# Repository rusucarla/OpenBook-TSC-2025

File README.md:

# Proiect TSC 2025 - OpenBook

## 1.O diagramă bloc cu toate componentele proiectului și cum sunt ele legate

```mermaid
graph TD
    
    USB["USB-C Connector(ESD Protection)"] -->|5V| CHG["Battery Charger (MCP73831)"]
    CHG -->|Charging| BATT["Li-Po Battery (2500mAh)"]
    BATT --> LDO["3.3V LDO Regulator (XC6220)"]

    LDO -->|3.3V| ESP["ESP32-C6-WROOM-1(MCU)"]

    ESP -- I2C --> RTC["Real Time Clock(DS3231)"]
    ESP -- I2C --> BME["Environmental Sensor(BME688)"]
    ESP -- I2C --> FUEL["Battery Fuel Gauge(MAX17048)"]
    ESP -- I2C --> QWIIC["Qwiic / Stemma QT"]

    ESP -- SPI --> FLASH["External NOR Flash(W25Q512)"]
    ESP -- SPI --> SD["MicroSD Card Slot"]
    ESP -- SPI --> EPD_HEADER["E-Paper Display Header"]

    EPD_HEADER --> EPD_DRIVER["EPD Driver Circuit"]
    EPD_DRIVER --> EPD_POW["EPD HV Power"]
    LDO --> EPD_HEADER

    ESP -- GPIO --> BUTTONS["3x Buttons:BOOT, CHANGE, RESET"]

    USB -- USB D+/D- --> ESP
```
## 2. BOM-ul (coloanele cu N/A sunt duplicate ale unui tip de componentă și am pus date doar la prima apariție a acelui tip de componentă)

Încă o observație, TP-ul si SJ-urile au fost modelate de către mine și astfel nu au model cu link sau data sheet.

| Name of component | Device                                       | Check Prices                                                                                                | DataSheet                                                                                                 |
|-------------------|----------------------------------------------|-----------------------------------------------------------------------------------------------------------------|---------------------------------------------------------------------------------------------------------------|
| BOOT_BUTTON       | BUTTON_CUSYOMV1                             | https://industry.panasonic.com/global/en/products/control/switch/light-touch/number/evqpuj02k                  | https://industry.panasonic.com/global/en/products/control/switch/light-touch/number/evqpuj02k                  |
| C1                | ESP32_WROVER_EAGLE-LTSPICE_CC0402            | https://industry.panasonic.com/global/en/products/control/switch/light-touch/number/evqpuj02k                  | https://industry.panasonic.com/global/en/products/control/switch/light-touch/number/evqpuj02k                  |
| C1_BAT            | ESP32_WROVER_EAGLE-LTSPICE_CC0402            | #N/A                                                                                                            | #N/A                                                                                                           |
| C1_BAT1           | EAGLE-LTSPICE_CC0402                         | #N/A                                                                                                            | #N/A                                                                                                           |
| C1_BAT2           | EAGLE-LTSPICE_CC0402                         | #N/A                                                                                                            | #N/A                                                                                                           |
| C2                | ESP32_WROVER_EAGLE-LTSPICE_CC0402            | #N/A                                                                                                            | #N/A                                                                                                           |
| C2_BAT\           | ESP32_WROVER_EAGLE-LTSPICE_CC0402            | #N/A                                                                                                            | #N/A                                                                                                           |
| C3                | RCL_CPOL-EUCT3528                            | #N/A                                                                                                            | #N/A                                                                                                           |
| C4                | ESP32_WROVER_EAGLE-LTSPICE_CC0402            | #N/A                                                                                                            | #N/A                                                                                                           |
| C4_USB            | ESP32_WROVER_EAGLE-LTSPICE_CC0402            | #N/A                                                                                                            | #N/A                                                                                                           |
| C5                | ESP32_WROVER_EAGLE-LTSPICE_CC0402            | #N/A                                                                                                            | #N/A                                                                                                           |
| C5_USB            | ESP32_WROVER_EAGLE-LTSPICE_CC0402            | #N/A                                                                                                            | #N/A                                                                                                           |
| C6                | ESP32_WROVER_EAGLE-LTSPICE_CC0402            | #N/A                                                                                                            | #N/A                                                                                                           |
| C7                | ESP32_WROVER_EAGLE-LTSPICE_CC0402            | #N/A                                                                                                            | #N/A                                                                                                           |
| C8                | ESP32_WROVER_EAGLE-LTSPICE_CC0402            | #N/A                                                                                                            | #N/A                                                                                                           |
| C9                | EAGLE-LTSPICE_CC0402                         | #N/A                                                                                                            | #N/A                                                                                                           |
| C10               | ESP32_WROVER_EAGLE-LTSPICE_CC0402            | #N/A                                                                                                            | #N/A                                                                                                           |
| C10_SUPERCAP      | CPH3225A                                     | https://www.snapeda.com/parts/CPH3225A/Seiko+Instruments/view-part/?ref=eda                                   | https://www.snapeda.com/parts/CPH3225A/Seiko+Instruments/view-part/?ref=eda                                   |
| CHANGE_BUTTON     | BUTTON_CUSYOMV1                             | https://industry.panasonic.com/global/en/products/control/switch-light-touch/number/evqpuj02k                  | https://industry.panasonic.com/global/en/products/control/switch-light-touch/number/evqpuj02k                  |
| CHG_LED           | ADAFRUIT_LEDCHIP-LED0603                     | https://www.snapeda.com/parts/KP-1608SURCK/Kingbright/view-part/?ref=search&t=LED%200603                       | https://www.snapeda.com/parts/KP-1608SURCK/Kingbright/view-part/?ref=search&t=LED%200603                       |
| C_DELAY           | ESP32_WROVER_EAGLE-LTSPICE_CC0402            | #N/A                                                                                                            | #N/A                                                                                                           |
| D1                | USBLC6-2SC6Y                                 | https://www.snapeda.com/parts/USBLC6-2SC6Y/STMicroelectronics/view-part/?ref=eda                              | https://www.snapeda.com/parts/USBLC6-2SC6Y/STMicroelectronics/view-part/?ref=eda                              |
| D2                | ESP32_WROVER_AVX---SD0805S020S1R0_AVX_...    | https://eu.mouser.com/ProductDetail/KYOCERA-AVX/SD0805S020S1R0?qs=jCA%252BPfw4LHbpkAoSnwrdjw%3D%3D              | http://datasheets.avx.com/schottky.pdf                                                                         |
| D3                | MBR0530                                      | https://eu.mouser.com/ProductDetail/KYOCERA-AVX/SD0805S020S1R0?qs=jCA%252BPfw4LHbpkAoSnwrdjw%3D%3D              | https://eu.mouser.com/ProductDetail/KYOCERA-AVX/SD0805S020S1R0?qs=jCA%252BPfw4LHbpkAoSnwrdjw%3D%3D              |
| D4                | MBR0530                                      | https://www.snapeda.com/parts/MBR0530/Onsemi/view-part/?ref=eda                                                | https://www.snapeda.com/parts/MBR0530/Onsemi/view-part/?ref=eda                                                |
| D5                | MBR0530                                      | https://www.snapeda.com/parts/MBR0530/Onsemi/view-part/?ref=eda                                                | https://www.snapeda.com/parts/MBR0530/Onsemi/view-part/?ref=eda                                                |
| D6                | PGB1010603MR                                 | https://www.snapeda.com/parts/PGB1010603MR/Littelfuse/view-part/?ref=eda                                      | https://www.snapeda.com/parts/PGB1010603MR/Littelfuse/view-part/?ref=eda                                      |
| D7                | ESP32_WROVER_AVX---SD0805S020S1R0_AVX_...    | https://eu.mouser.com/ProductDetail/KYOCERA-AVX/SD0805S020S1R0?qs=jCA%252BPfw4LHbpkAoSnwrdjw%3D%3D              | http://datasheets.avx.com/schottky.pdf                                                                         |
| D8                | PGB1010603MR                                 | https://www.snapeda.com/parts/PGB1010603MR/Littelfuse/view-part/?ref=eda                                      | https://www.snapeda.com/parts/PGB1010603MR/Littelfuse/view-part/?ref=eda                                      |
| D9                | PGB1010603MR                                 | https://www.snapeda.com/parts/PGB1010603MR/Littelfuse/view-part/?ref=eda                                      | https://www.snapeda.com/parts/PGB1010603MR/Littelfuse/view-part/?ref=eda                                      |
| D10               | PGB1010603MR                                 | https://www.snapeda.com/parts/PGB1010603MR/Littelfuse/view-part/?ref=eda                                      | https://www.snapeda.com/parts/PGB1010603MR/Littelfuse/view-part/?ref=eda                                      |
| D11               | PGB1010603MR                                 | https://www.snapeda.com/parts/PGB1010603MR/Littelfuse/view-part/?ref=eda                                      | https://www.snapeda.com/parts/PGB1010603MR/Littelfuse/view-part/?ref=eda                                      |
| D12               | PGB1010603MR                                 | https://www.snapeda.com/parts/PGB1010603MR/Littelfuse/view-part/?ref=eda                                      | https://www.snapeda.com/parts/PGB1010603MR/Littelfuse/view-part/?ref=eda                                      |
| EPD_C1            | ESP32_WROVER_EAGLE-LTSPICE_CC0402            | #N/A                                                                                                            | #N/A                                                                                                           |
| EPD_C2            | ESP32_WROVER_EAGLE-LTSPICE_CC0402            | #N/A                                                                                                            | #N/A                                                                                                           |
| EPD_C5            | ESP32_WROVER_EAGLE-LTSPICE_CC0402            | #N/A                                                                                                            | #N/A                                                                                                           |
| EPD_C6            | ESP32_WROVER_EAGLE-LTSPICE_CC0402            | #N/A                                                                                                            | #N/A                                                                                                           |
| EPD_C7            | ESP32_WROVER_EAGLE-LTSPICE_CC0402            | #N/A                                                                                                            | #N/A                                                                                                           |
| EPD_C8            | ESP32_WROVER_EAGLE-LTSPICE_CC0402            | #N/A                                                                                                            | #N/A                                                                                                           |
| EPD_C9            | ESP32_WROVER_EAGLE-LTSPICE_CC0402            | #N/A                                                                                                            | #N/A                                                                                                           |
| EPD_C10           | ESP32_WROVER_EAGLE-LTSPICE_CC0402            | #N/A                                                                                                            | #N/A                                                                                                           |
| EPD_C11           | ESP32_WROVER_EAGLE-LTSPICE_CC0402            | #N/A                                                                                                            | #N/A                                                                                                           |
| EPD_C12           | ESP32_WROVER_EAGLE-LTSPICE_CC0402            | #N/A                                                                                                            | #N/A                                                                                                           |
| IC1               | BD5229G-TR                                   | https://componentsearchengine.com/part-view/BD5229G-TR/ROHM%20Semiconductor                                    | https://componentsearchengine.com/part-view/BD5229G-TR/ROHM%20Semiconductor                                    |
| IC4               | XC6220A331MR-G                               | https://componentsearchengine.com/part-view/XC6220A331MR-G/Torex                                              | https://componentsearchengine.com/part-view/XC6220A331MR-G/Torex                                              |
| J1                | FH34SRJ-24S-0.5SH_99_                        | https://componentsearchengine.com/part-view/XC6220A331MR-G/Torex                                              | https://componentsearchengine.com/part-view/XC6220A331MR-G/Torex                                              |
| J2                | SAMACSYS_PARTS_USB4110-GF-A                  | https://componentsearchengine.com/part-view/USB4110-GF-A/GCT%20(GLOBAL%20CONNECTOR%20TECHNOLOGY               | https://componentsearchengine.com/part-view/USB4110-GF-A/GCT%20(GLOBAL%20CONNECTOR%20TECHNOLOGY               |
| J3                | QWIIC_CONNECTORJS-1MM                        | #N/A                                                                                                            | #N/A                                                                                                           |
| J4                | 112A-TAAR-R03_ATTEND                         | https://store.comet.srl.ro/Catalogue/Product/43497/                                                            | https://store.comet.srl.ro/Catalogue/Product/43497/                                                            |
| L1                | 744043680IND_4828-WE-TPC_WRE                 | https://eu.mouser.com/ProductDetail/Wurth-Elektronik/744043680?qs=PGXP4M47uW6VkZq%252BkzjrHA%3D%3D               | https://eu.mouser.com/ProductDetail/Wurth-Elektronik/744043680?qs=PGXP4M47uW6VkZq%252BkzjrHA%3D%3D               |
| PFMF.050.1        | ESP32C6_VARISTORCN1812                       | https://www.mouser.co.uk/ProductDetail/EPCOS-TDK/B72520T0350K062?qs=dEfas%2FXlABIszF52uu7vrg%3D%3D              | https://www.mouser.co.uk/ProductDetail/EPCOS-TDK/B72520T0350K062?qs=dEfas%2FXlABIszF52uu7vrg%3D%3D              |
| Q1                | ESP32_WROVER_SPARKFUN-DISCRETESEMI_MOSFET_...| https://componentsearchengine.com/part-view/DMG2305UX-7/Diodes%20Incorporated                                  | https://componentsearchengine.com/part-view/DMG2305UX-7/Diodes%20Incorporated                                  |
| Q2                | ESP32_WROVER_SPARKFUN-DISCRETESEMI_MOSFET_...| #N/A                                                                                                            | #N/A                                                                                                           |
| Q3                | D8                                           | https://componentsearchengine.com/part-view/SI1308EDL-T1-GE3/Vishay                                           | https://componentsearchengine.com/part-view/SI1308EDL-T1-GE3/Vishay                                           |
| R1                | ESP32_WROVER_EAGLE-LTSPICE_RR0402            | #N/A                                                                                                            | #N/A                                                                                                           |
| R1-PINH           | ESP32_WROVER_EAGLE-LTSPICE_RR0402            | #N/A                                                                                                            | #N/A                                                                                                           |
| R1-PINH1          | ESP32_WROVER_EAGLE-LTSPICE_RR0402            | #N/A                                                                                                            | #N/A                                                                                                           |
| R1_BAT            | ESP32_WROVER_EAGLE-LTSPICE_RR0402            | #N/A                                                                                                            | #N/A                                                                                                           |
| R1_PWRUSB         | ESP32_WROVER_EAGLE-LTSPICE_RR0402            | #N/A                                                                                                            | #N/A                                                                                                           |
| R2                | ESP32_WROVER_EAGLE-LTSPICE_RR0402            | https://componentsearchengine.com/part-view/R0402%201%25%20100%20K%20(RC0402FR-07100KL                         | https://componentsearchengine.com/part-view/R0402%201%25%20100%20K%20(RC0402FR-07100KL                         |
| R2-PINH           | ESP32_WROVER_EAGLE-LTSPICE_RR0402            | #N/A                                                                                                            | #N/A                                                                                                           |
| R2-PINH1          | ESP32_WROVER_EAGLE-LTSPICE_RR0402            | #N/A                                                                                                            | #N/A                                                                                                           |
| R2-USB            | ESP32_WROVER_EAGLE-LTSPICE_RR0402            | #N/A                                                                                                            | #N/A                                                                                                           |
| R2-USB1           | ESP32_WROVER_EAGLE-LTSPICE_RR0402            | #N/A                                                                                                            | #N/A                                                                                                           |
| R2_BAT            | ESP32_WROVER_EAGLE-LTSPICE_RR0402            | #N/A                                                                                                            | #N/A                                                                                                           |
| R3                | ESP32_WROVER_EAGLE-LTSPICE_RR0402            | #N/A                                                                                                            | #N/A                                                                                                           |
| R4                | ESP32_WROVER_EAGLE-LTSPICE_RR0402            | #N/A                                                                                                            | #N/A                                                                                                           |
| R5                | ESP32_WROVER_EAGLE-LTSPICE_RR0402            | #N/A                                                                                                            | #N/A                                                                                                           |
| R6                | ESP32_WROVER_EAGLE-LTSPICE_RR0402            | #N/A                                                                                                            | #N/A                                                                                                           |
| R7                | ESP32_WROVER_EAGLE-LTSPICE_RR0402            | #N/A                                                                                                            | #N/A                                                                                                           |
| R8                | ESP32_WROVER_EAGLE-LTSPICE_RR0402            | #N/A                                                                                                            | #N/A                                                                                                           |
| R9                | ESP32_WROVER_EAGLE-LTSPICE_RR0402            | #N/A                                                                                                            | #N/A                                                                                                           |
| R10               | ESP32_WROVER_EAGLE-LTSPICE_RR0402            | #N/A                                                                                                            | #N/A                                                                                                           |
| RESET_BUTTON      | BUTTON_CUSYOMV1                             | https://industry.panasonic.com/global/en/products/control/switch/light-touch/number/evqpuj02k                  | https://industry.panasonic.com/global/en/products/control/switch/light-touch/number/evqpuj02k                  |
| R_BOOT            | ESP32_WROVER_EAGLE-LTSPICE_RR0402            | #N/A                                                                                                            | #N/A                                                                                                           |
| R_CAPACITOR       | ESP32_WROVER_EAGLE-LTSPICE_RR0402            | #N/A                                                                                                            | #N/A                                                                                                           |
| R_CHANGE          | ESP32_WROVER_EAGLE-LTSPICE_RR0402            | #N/A                                                                                                            | #N/A                                                                                                           |
| R_CL1             | ESP32_WROVER_EAGLE-LTSPICE_RR0402            | #N/A                                                                                                            | #N/A                                                                                                           |
| R_RESET           | ESP32_WROVER_EAGLE-LTSPICE_RR0402            | #N/A                                                                                                            | #N/A                                                                                                           |
| SENSOR2           | ESP32_WROVER_BME680_BME680                   | https://www.snapeda.com/parts/BME680/Bosch/view-part/?welcome=home                                            | https://www.snapeda.com/parts/BME680/Bosch/view-part/?welcome=home                                            |
| SJ1              | SJ                                           | https://grabcad.com/library/solder-jumpers-1                                                                   | https://grabcad.com/library/solder-jumpers-1                                                                   |
| TP1               | TPTP20R                                      | #N/A                                                                                                            | #N/A                                                                                                           |
| TP2               | TPTP20R                                      | #N/A                                                                                                            | #N/A                                                                                                           |
| TP3               | TPTP20R                                      | #N/A                                                                                                            | #N/A                                                                                                           |
| TP4               | TPTP20R                                      | #N/A                                                                                                            | #N/A                                                                                                           |
| TP5               | TPTP20R                                      | #N/A                                                                                                            | #N/A                                                                                                           |
| TP6               | TPTP20R                                      | #N/A                                                                                                            | #N/A                                                                                                           |
| TP7               | TPTP20R                                      | #N/A                                                                                                            | #N/A                                                                                                           |
| TP8               | TPTP20R                                      | #N/A                                                                                                            | #N/A                                                                                                           |
| TP9               | TPTP20R                                      | #N/A                                                                                                            | #N/A                                                                                                           |
| TP10              | TPTP20R                                      | #N/A                                                                                                            | #N/A                                                                                                           |
| TP11              | TPTP20R                                      | #N/A                                                                                                            | #N/A                                                                                                           |
| TP12              | TPTP20R                                      | #N/A                                                                                                            | #N/A                                                                                                           |
| TP13              | TPTP20R                                      | #N/A                                                                                                            | #N/A                                                                                                           |
| TP14              | TPTP20R                                      | #N/A                                                                                                            | #N/A                                                                                                           |
| TP15              | TPTP20R                                      | #N/A                                                                                                            | #N/A                                                                                                           |
| TP16              | TPTP20R                                      | #N/A                                                                                                            | #N/A                                                                                                           |
| TP17              | TPTP20R                                      | #N/A                                                                                                            | #N/A                                                                                                           |
| U1                | W25Q512JVEIQ                                 | https://www.snapeda.com/parts/W25Q512JVEIQ/Winbond+Electronics/view-part/?ref=eda                             | https://www.snapeda.com/parts/W25Q512JVEIQ/Winbond+Electronics/view-part/?ref=eda                             |
| U2                | ESP32-C6-WROOM-1-N8                          | https://www.snapeda.com/parts/ESP32-C6-WROOM-1-N8/Espressif+Systems/view-part/?ref=eda                        | https://www.snapeda.com/parts/ESP32-C6-WROOM-1-N8/Espressif+Systems/view-part/?ref=eda                        |
| U3                | DS3231SN#                                    | https://www.snapeda.com/parts/DS3231SN%23/Analog+Devices/view-part/?ref=eda                                   | https://www.snapeda.com/parts/DS3231SN%23/Analog+Devices/view-part/?ref=eda                                   |
| U4                | MAX17048G+T10                                | https://www.snapeda.com/parts/MAX17048G+T10/Analog+Devices/view-part/?ref=eda                                 | https://www.snapeda.com/parts/MAX17048G+T10/Analog+Devices/view-part/?ref=eda                                 |
| U5                | ESP32_WROVER_SPARKFUN-IC-POWER_MCP73831      | https://eu.mouser.com/ProductDetail/Microchip-Technology/MCP73831T-2ACI-OT?qs=yUQqVecv4qvbBQBGbHx0Mw%3D%3Dcf   | https://eu.mouser.com/ProductDetail/Microchip-Technology/MCP73831T-2ACI-OT?qs=yUQqVecv4qvbBQBGbHx0Mw%3D%3Dcf   |

## 3. Descrierea in detaliu a functionalitatilor hardware 

### 1. Microcontroller – ESP32-C6

- **Procesor**: 32-bit RISC-V, cu frecvență de până la 160MHz.
    
- **Memorie**: 512KB SRAM intern și 8MB flash extern (W25Q512JVEIQ).
    
- **Conectivitate**: Wi-Fi 6 (802.11ax), Bluetooth 5 (LE), USB 2.0 (full-speed).
    
- **Periferice**: SPI, I²C, UART, GPIO multiple.
    
- **Consum**: Posibilitate de moduri low-power (sleep, deep sleep).
---

### 2. Afișajul E-Paper (7.5 inch)

- **Model**: Waveshare (sau echivalent) cu rezoluție 800×480.
    
- **Interfață**: 4-wire SPI + semnale de control (CS, DC, RST, BUSY).
    
- **Consum**: Foarte redus în mod static (după refresh), dar necesită un curent mai mare în timpul refresh-ului (aprox. 15–25mA, în funcție de modul de actualizare).

**De ce l-am ales?**  
E-paper consumă energie doar când reîmprospătează imaginea. Este ideal pentru un e-reader, deoarece menține afișajul vizibil fără consum suplimentar.

---

### 3. Senzor de Mediu – BME688

- **Parametri măsurați**: Temperatură, Umiditate, Presiune și Calitate aer (VOC/eCO2).
    
- **Interfață**: I²C la 400kHz (SDA și SCL).
    
- **Consum**: Foarte mic (în jur de 2.1µA în standby și până la câteva mA în mod de măsurare).

**De ce BME688?**  
Integrează într-un singur cip mai multe tipuri de măsurători de mediu, util pentru a afișa date despre condițiile de citire (temperatură, umiditate etc.).

---

### 4. Baterie și Managementul Energiei

- **Baterie Li-Po 2500mAh** (3.7V nominal).
    
- **IC de Încărcare**: MCP73831 (Microchip) – încărcare Li-Po prin USB-C (până la 1A).
    
- **Fuel Gauge**: MAX17048 – monitorizează nivelul de încărcare, tensiunea și starea bateriei (I²C).
    
- **LDO**: XC6220A331MR-G (exemplu) sau echivalent, pentru a asigura 3.3V stabil pentru microcontroller și restul componentelor.

**De ce aceste componente?**

- MCP73831 este un controler simplu, fiabil și compatibil cu USB.
    
- MAX17048 oferă date precise despre nivelul bateriei și poate alerta asupra unei baterii descărcate.

---

### 5. Butoane (3x Tactile Switch)

- **Tip**: Tactile switch Panasonic (sau echivalent).
    
- **Funcții**: Navigare meniu, selectare opțiune, întoarcere pagină etc.
    
- **Conexiune**: Fiecare buton se leagă la un GPIO al ESP32-C6 printr-un circuit de debouncing (rezistență și condensator) sau se poate face debouncing în firmware.

---

### 6. USB-C Port

- **Rol**: Încărcare baterie + Transfer de date (USB 2.0 full-speed).
    
- **Protecții**: ESD (USBLC6-2SC6Y) + rezistențe de terminare.
    
- **Posibilitate**: Actualizări firmware prin USB (bootloader + tool extern) sau direct OTA prin Wi-Fi.

---

### 7. Conector Qwiic (I²C)

- Conector standard cu 4 pini: VCC, GND, SDA, SCL.
    
- Permite atașarea rapidă a altor senzori sau module I²C (expansiune, testare, prototipare rapidă).

---

### 8. SD Memory Card Connector (112A-TAAR-R03)

- **Rol**: Posibilitate de stocare externă pentru e-book-uri, log-uri sau update-uri firmware.
    
- **Interfață**: Poate fi SD (1-bit / 4-bit) sau SPI, în funcție de configurația firmware-ului.

---

### 9. RTC – DS3231

- **Funcție**: Asigură un ceas de timp real foarte precis.
    
- **Interfață**: I²C (aceeași magistrală cu BME688 și MAX17048).
    
- **Backup**: Supercondensator sau baterie secundară pentru a menține timpul și în absența alimentării principale.

---

### 10. Memorii Suplimentare

- **W25Q512JVEIQ** (Flash extern) – conectat la ESP32-C6 prin SPI dedicat (quad SPI).
    
    - Aici se stochează firmware-ul și datele mari (e-book-uri etc.).

---

### Comunicarea și Interfețele

1. **SPI**:
    
    - Ecranul e-paper (4-wire SPI).
        
    - Flash extern (quad SPI dedicat, pinii sunt în mare parte fixați de designul ESP32-C6).
        
2. **I²C**:
    
    - Senzorul BME688.
        
    - Fuel Gauge MAX17048.
        
    - RTC DS3231.
        
    - Qwiic Connector (pentru potențiale extensii).
        
3. **USB 2.0**:
    
    - Date + alimentare/încărcare prin USB-C.
        
4. **GPIO**:
    
    - Butoane (3x intrări digitale).
        
    - Eventual semnale de control suplimentare (reset display, busy pin display, semnal de enable alimentare etc.).

### Calcul Simplificat al Consumului

| Modul                     | Consum tipic                           |
| ------------------------- | -------------------------------------- |
| **ESP32-C6** (activ)      | ~80mA (Wi-Fi activ) / < 10mA (idle)    |
| **E-Paper** (refresh)     | ~15–25mA (doar în timpul refresh-ului) |
| **BME688** (activ)        | ~3.6mA (peak) / 2.1µA (sleep)          |
| **MAX17048** (fuel gauge) | ~50µA                                  |
| **DS3231** (RTC)          | ~3.5mA (activ) / <1µA (back-up)        |
| **MCP73831** (charger)    | Consum diferit în funcție de curentul de încărcare:<br>- *500 mA* (standard)<br>- *1 A* (dacă design-ul suportă încărcare mai rapidă)       |

#### Mod Activ + Wi-Fi

- În timpul activării Wi-Fi (pentru descărcarea e-book-urilor sau actualizarea conținutului) și al refresh-ului ecranului e-paper, **consumul total** al sistemului (ESP32-C6 + e-paper + senzori) poate ajunge la **100–150 mA**.  
- Această valoare **include** ESP32-C6 în mod Wi-Fi activ, senzori și curentul suplimentar de ~15–25 mA în timpul refresh-ului e-paper.

#### Deep Sleep / Standby

- **ESP32-C6** poate intra în deep sleep cu un consum de ordinul zecilor de microamperi (~70 µA dacă este bine optimizat și cu periferice oprite).  
- Ceilalți senzori și componente pot fi dezactivați sau puși în moduri de consum redus, contribuind cu încă câțiva µA (RTC, fuel gauge etc.).  
- Totalul în deep sleep poate fi menținut sub **100 µA** dacă sunt implementate corect modurile de consum redus pentru fiecare componentă.

#### Exemplu de Calcul pentru Autonomie

Cu o **baterie de 2500 mAh**, considerăm un ciclu de funcționare ipotetic:

- **95% din timp** dispozitivul este în deep sleep (~70 µA).  
- **5% din timp** este în mod activ (~120 mA), cu Wi-Fi pornit și e-paper folosit.  

1. **Consum în deep sleep (95% din timp)**  
     $I_{\mathrm{deep\_sleep}} = 70\,\mu A$
   
3. **Consum în mod activ (5% din timp)**  
   $I_{\mathrm{activ}} \approx 120\,mA$

4. **Media consumului orar**  
   $I_{\mathrm{mediu}} = 0.95 \times 70\,\mu A + 0.05 \times 120\,mA = (0.95 \times 0.07\,mA) + (0.05 \times 120\,mA) = 0.0665\,mA + 6\,mA = \approx 6.07\,mA$

5. **Autonomie teoretică**  
   $\text{Autonomie} = \frac{Capacitatea\ Bateriei}{I_{\mathrm{mediu}}}
     \approx \frac{2500\,mAh}{6.07\,mA} \approx 412\,ore \approx 17\,zile$

Dacă mai optimizăm timpul activ (de exemplu, îl reducem la 2–3% din timp) sau scădem consumul de vârf, se poate ajunge la **3–4 săptămâni**. Totuși, în practică, autonomia depinde foarte mult de:

- **Frecvența refresh-ului** e-paper  
- **Durata și frecvența conexiunilor Wi-Fi**  
- **Alți consumatori** (de ex. LED-uri de stare sau module suplimentare)

## 4. Descrieți în detaliu ce pini ai ESP32-C6 sunt folosiți pentru fiecare componentă și de ce

| Pin ESP32-C6    | Componentă / Semnal                       | De ce?                                                        |
| --------------- | ----------------------------------------- | ------------------------------------------------------------- |
| **GPIO1 (SDA)** | I²C SDA (BME688, MAX17048, DS3231, Qwiic) | Partajare magistrală I²C pentru toți senzorii și RTC.         |
| **GPIO2 (SCL)** | I²C SCL (BME688, MAX17048, DS3231, Qwiic) | Linia de clock pentru I²C.                                    |
| **GPIO5**       | SPI MISO (E-Paper)                        | Citirea datelor/statusului display-ului (dacă e suportat).    |
| **GPIO6**       | SPI MOSI (E-Paper)                        | Trimiterea datelor către e-paper.                             |
| **GPIO7**       | SPI CLK (E-Paper)                         | Semnal de clock pentru e-paper.                               |
| **GPIO8**       | SPI CS (E-Paper)                          | Chip Select pentru e-paper.                                   |
| **GPIO9**       | E-Paper DC (Data/Command)                 | Semnal care diferențiază datele de comenzile pentru afișaj.   |
| **GPIO10**      | E-Paper RST                               | Reset hardware pentru e-paper.                                |
| **GPIO11**      | E-Paper BUSY                              | Intrare din display, indică dacă este ocupat.                 |
| **GPIO12**      | Button #1                                 | Intrare digitală pentru buton (ex. NEXT page).                |
| **GPIO13**      | Button #2                                 | Intrare digitală pentru buton (ex. PREV page).                |
| **GPIO14**      | Button #3                                 | Intrare digitală pentru buton (ex. MENU/OK).                  |
| **GPIO15**      | MAX17048 ALERT (opțional)                 | Avertizare nivel baterie scăzut.                              |
| **GPIO16**      | USB D+ (intern la USB PHY)                | Pin dedicat pentru USB 2.0. (În mod normal pin hardware fix). |
| **GPIO17**      | USB D- (intern la USB PHY)                | Pin dedicat pentru USB 2.0. (La fel, pin fix).                |
| **GPIO18**      | LED de status (opțional)                  | Indicator pentru diverse stări (Wi-Fi, încărcare, etc.).      |
| **GPIO19**      | SD Card CS (opțional)                     | Chip Select pentru cardul SD (dacă se folosește SPI).         |
| **GPIO20**      | SD Card MISO (opțional)                   | Intrare date de la card SD.                                   |
| **GPIO21**      | SD Card MOSI (opțional)                   | Ieșire date către card SD.                                    |
| **GPIO4**       | SD Card CLK (opțional)                    | Semnal de clock pentru card SD (SPI).                         |

## Orice altceva 

Design log-ul poate fi gasit pe [autodesk](https://a360.co/4kX1RTV)

Exista o incompatibilitate intre .fbrd si .brd cand vine vorba de via stching. Am pus si fisierul .fbrd pentru a se oberva diferenta.

Am decis sa redenumesc TP-urile pentru a fi mai usor de gestionat.

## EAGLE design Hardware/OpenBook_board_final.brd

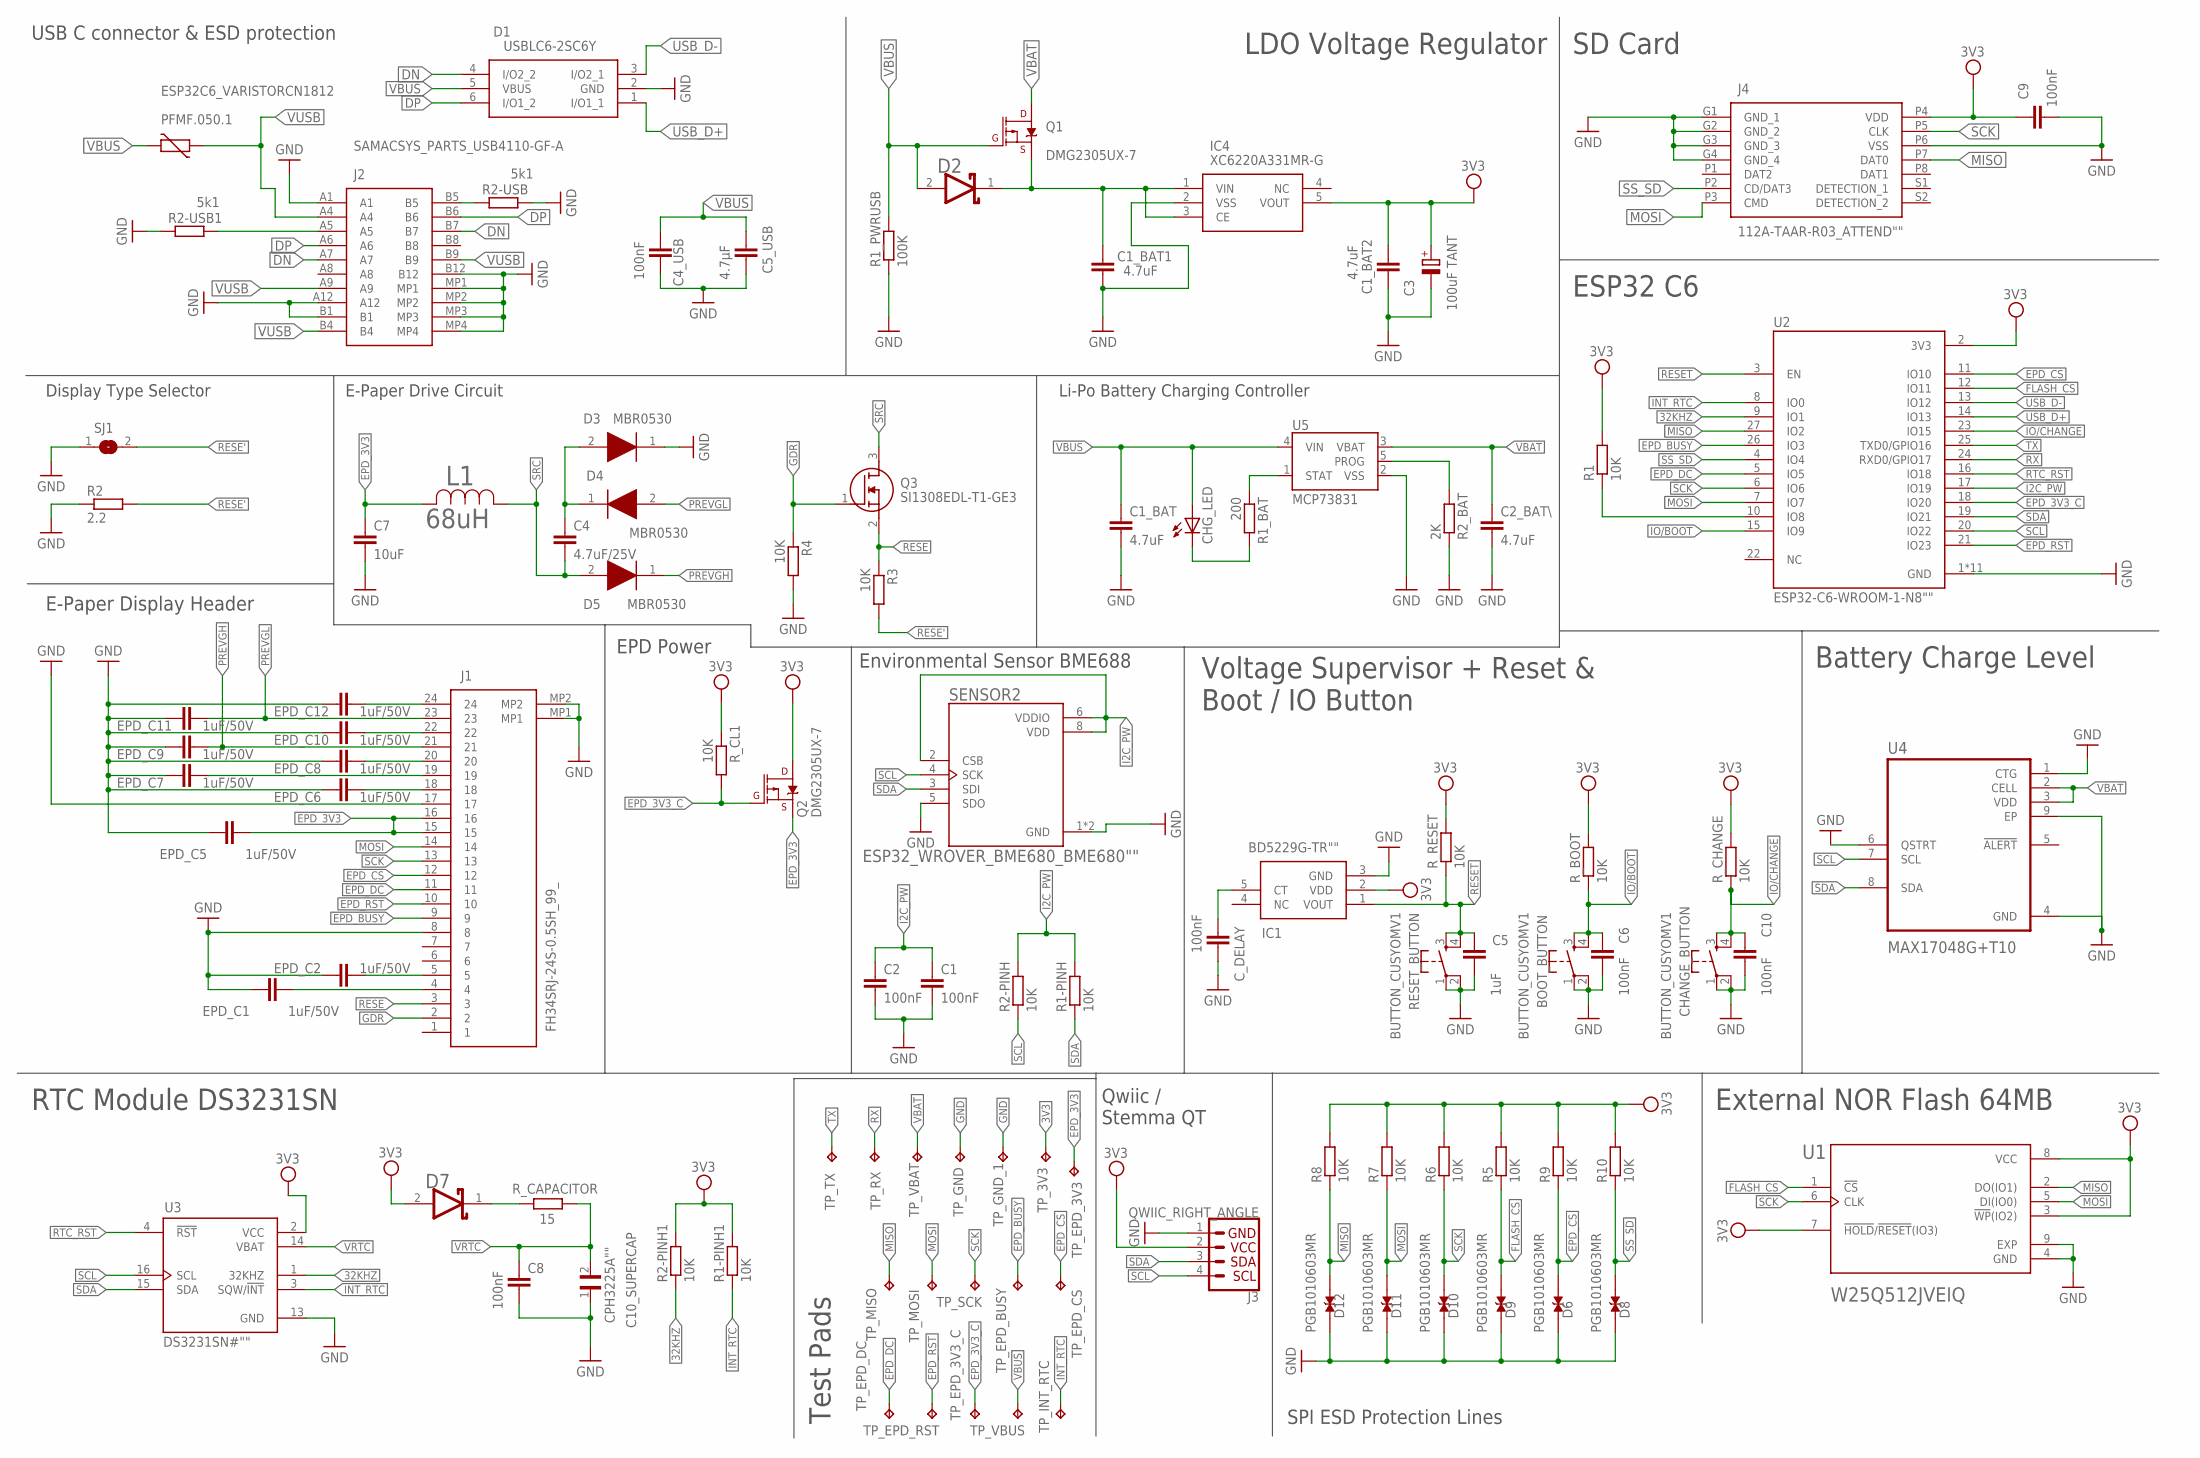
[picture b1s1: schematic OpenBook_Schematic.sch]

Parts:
BOOT_BUTTON: BUTTON_CUSYOMV1; MYBUTTON
C1, C2, C4_USB, C6, C8, C9, C10: 100nF; ESP32_WROVER_EAGLE-LTSPICE_C0402
C1_BAT, C1_BAT1, C1_BAT2, C2_BAT\: 4.7uF; ESP32_WROVER_EAGLE-LTSPICE_C0402
C3: 100uF TANT; RCL_CT3528
C4: 4.7uF/25V; ESP32_WROVER_EAGLE-LTSPICE_C0402
C5: 1uF; ESP32_WROVER_EAGLE-LTSPICE_C0402
C5_USB: 4.7μF; ESP32_WROVER_EAGLE-LTSPICE_C0402
C7: 10uF; ESP32_WROVER_EAGLE-LTSPICE_C0402
C10_SUPERCAP: CPH3225A""; CAPCP3225X100N
CHANGE_BUTTON: BUTTON_CUSYOMV1; MYBUTTON
CHG_LED: ADAFRUIT_LEDCHIP-LED0603; ADAFRUIT_CHIP-LED0603
C_DELAY: 100nF; ESP32_WROVER_EAGLE-LTSPICE_C0402
D1: USBLC6-2SC6Y; SOT95P280X145-6N
D2, D7: ESP32_WROVER_AVX---SD0805S020S1R0_AVX_SD0805S020S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; ESP32_WROVER_AVX---SD0805S020S1R0_AVX_SD0805S020S1R0_0
D3, D4, D5: MBR0530; SOD3716X135N
D6, D8, D9, D10, D11, D12: PGB1010603MR; DIOC1608X36N
EPD_C1, EPD_C2, EPD_C5, EPD_C6, EPD_C7, EPD_C8, EPD_C9, EPD_C10, EPD_C11, EPD_C12: 1uF/50V; ESP32_WROVER_EAGLE-LTSPICE_C0402
IC1: BD5229G-TR""; SOT95P280X125-5N
IC4: XC6220A331MR-G; SOT95P280X120-5N
J1: FH34SRJ-24S-0.5SH_99_; FH34SRJ24S05SH99
J2: SAMACSYS_PARTS_USB4110-GF-A; SAMACSYS_PARTS_USB4110GFA
J3: QWIIC_RIGHT_ANGLE; JST04_1MM_RA
J4: 112A-TAAR-R03_ATTEND""; 112ATAARR03ATTEND
L1: 68uH; IND_4828-WE-TPC_WRE
PFMF.050.1: ESP32C6_VARISTORCN1812; ESP32C6_VARISTOR_CT/CN1812
Q1, Q2: 20V/4.2A/52mΩ/1.4W; ESP32_WROVER_SPARKFUN-DISCRETESEMI_SOT23-3; PARTNAME DMG2305UX-7
Q3: SI1308EDL-T1-GE3; SOT65P210X110-3N
R1, R1-PINH, R1-PINH1, R2-PINH, R2-PINH1, R3, R4, R5, R6, R7, R8, R9, R10: 10K; ESP32_WROVER_EAGLE-LTSPICE_R0402
R1_BAT: 200; ESP32_WROVER_EAGLE-LTSPICE_R0402
R1_PWRUSB: 100K; ESP32_WROVER_EAGLE-LTSPICE_R0402
R2: 2.2; ESP32_WROVER_EAGLE-LTSPICE_R0402
R2-USB, R2-USB1: 5k1; ESP32_WROVER_EAGLE-LTSPICE_R0402
R2_BAT: 2K; ESP32_WROVER_EAGLE-LTSPICE_R0402
RESET_BUTTON: BUTTON_CUSYOMV1; MYBUTTON
R_BOOT: 10K; ESP32_WROVER_EAGLE-LTSPICE_R0402
R_CAPACITOR: 15; ESP32_WROVER_EAGLE-LTSPICE_R0402
R_CHANGE: 10K; ESP32_WROVER_EAGLE-LTSPICE_R0402
R_CL1: 10K; ESP32_WROVER_EAGLE-LTSPICE_R0402
R_RESET: 10K; ESP32_WROVER_EAGLE-LTSPICE_R0402
SENSOR2: ESP32_WROVER_BME680_BME680""; ESP32_WROVER_BME680_PSON80P300X300X100-8N
SJ1: SJ
TP_3V3: TPTP20R; TP20R
TP_EPD_3V3, TP_EPD_3V3_C: TPTP20R; TP20R
TP_EPD_BUSY: TPTP20R; TP20R
TP_EPD_CS: TPTP20R; TP20R
TP_EPD_DC: TPTP20R; TP20R
TP_EPD_RST: TPTP20R; TP20R
TP_GND: TPTP20R; TP20R
TP_GND_1: TPTP20R; TP20R
TP_INT_RTC: TPTP20R; TP20R
TP_MISO: TPTP20R; TP20R
TP_MOSI: TPTP20R; TP20R
TP_RX: TPTP20R; TP20R
TP_SCK: TPTP20R; TP20R
TP_TX: TPTP20R; TP20R
TP_VBAT: TPTP20R; TP20R
TP_VBUS: TPTP20R; TP20R
U1: W25Q512JVEIQ; SON127P600X800X80-9N
U2: ESP32-C6-WROOM-1-N8""; XCVR_ESP32-C6-WROOM-1-N8
U3: DS3231SN#""; SOIC127P1032X265-16N
U4: MAX17048G+T10; SON50P200X200X80-9N
U5: MCP73831; ESP32_WROVER_SPARKFUN-IC-POWER_SOT23-5

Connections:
3V3: C1_BAT2.1, C3.+, C9.1, D7.2 (ANODE), IC1.2 (VDD), IC4.5 (VOUT), J3.2, J4.P4 (VDD), Q2.3 (D), R1.2, R1-PINH1.2, R2-PINH1.2, R5.2, R6.2, R7.2, R8.2, R9.2, R10.2, R_BOOT.2, R_CHANGE.2, R_CL1.1, R_RESET.2, TP_3V3.TP, U1.3 (!WP!(IO2)), U1.7 (!HOLD!/!RESET!(IO3)), U1.8 (VCC), U2.2 (3V3), U3.2 (VCC)
32KHZ: R2-PINH1.1, U2.9 (IO1), U3.1 (32KHZ)
DN: D1.4 (I/O2_2), J2.A7, J2.B7
DP: D1.6 (I/O1_2), J2.A6, J2.B6
EPD_3V3: C7.1, EPD_C5.1, J1.15, J1.16, L1.2, Q2.2 (S), TP_EPD_3V3.TP
EPD_3V3_C: Q2.1 (G), R_CL1.2, TP_EPD_3V3_C.TP, U2.18 (IO20)
EPD_BUSY: J1.9, TP_EPD_BUSY.TP, U2.26 (IO3)
EPD_CS: D6.2, J1.12, R9.1, TP_EPD_CS.TP, U2.11 (IO10)
EPD_DC: J1.11, TP_EPD_DC.TP, U2.5 (IO5)
EPD_RST: J1.10, TP_EPD_RST.TP, U2.21 (IO23)
FLASH_CS: D9.2, R5.1, U1.1 (!CS), U2.12 (IO11)
GDR: J1.2, Q3.1 (G), R4.1
GND: BOOT_BUTTON.1, BOOT_BUTTON.2, C1.2, C1_BAT.2, C1_BAT1.2, C1_BAT2.2, C2.2, C2_BAT\.2, C3.-, C4_USB.2, C5.2, C5_USB.2, C6.2, C7.2, C8.2, C9.2, C10.2, C10_SUPERCAP.1, CHANGE_BUTTON.1, CHANGE_BUTTON.2, C_DELAY.2, D1.2 (GND), D3.1 (K), D6.1, D8.1, D9.1, D10.1, D11.1, D12.1, EPD_C1.2, EPD_C2.2, EPD_C5.2, EPD_C6.2, EPD_C7.2, EPD_C8.2, EPD_C9.2, EPD_C10.2, EPD_C11.2, EPD_C12.2, IC1.3 (GND), IC4.2 (VSS), J1.8, J1.17, J1.MP1, J1.MP2, J2.A1, J2.A12, J2.B1, J2.B12, J2.MP1, J2.MP2, J2.MP3, J2.MP4, J3.1, J4.G1 (GND_1), J4.G2 (GND_2), J4.G3 (GND_3), J4.G4 (GND_4), J4.P6 (VSS), R1_PWRUSB.1, R2.1, R2-USB.2, R2-USB1.1, R2_BAT.1, R4.2, RESET_BUTTON.1, RESET_BUTTON.2, SENSOR2.1 (GND), SENSOR2.5 (SDO), SENSOR2.7 (GND), SJ1.1, TP_GND.TP, TP_GND_1.TP, U1.4 (GND), U1.9 (EXP), U2.1 (GND), U2.28 (GND), U2.29_1 (GND), U2.29_2 (GND), U2.29_3 (GND), U2.29_4 (GND), U2.29_5 (GND), U2.29_6 (GND), U2.29_7 (GND), U2.29_8 (GND), U2.29_9 (GND), U3.13 (GND), U4.1 (CTG), U4.4 (GND), U4.6 (QSTRT), U4.9 (EP), U5.2 (VSS)
I2C_PW: C1.1, C2.1, R1-PINH.2, R2-PINH.2, SENSOR2.2 (CSB), SENSOR2.6 (VDDIO), SENSOR2.8 (VDD), U2.17 (IO19)
INT_RTC: R1-PINH1.1, TP_INT_RTC.TP, U2.8 (IO0), U3.3 (SQW/!INT)
IO/BOOT: BOOT_BUTTON.3, BOOT_BUTTON.4, C6.1, R_BOOT.1, U2.15 (IO9)
IO/CHANGE: C10.1, CHANGE_BUTTON.3, CHANGE_BUTTON.4, R_CHANGE.1, U2.23 (IO15)
MISO: D12.2, J4.P7 (DAT0), R8.1, TP_MISO.TP, U1.2 (DO(IO1)), U2.27 (IO2)
MOSI: D11.2, J1.14, J4.P3 (CMD), R7.1, TP_MOSI.TP, U1.5 (DI(IO0)), U2.7 (IO7)
unnamed: J2.B5, R2-USB.1
unnamed: C1_BAT1.1, D2.1 (CATHODE), IC4.1 (VIN), IC4.3 (CE), Q1.2 (S)
unnamed: R1.1, U2.10 (IO8)
unnamed: D7.1 (CATHODE), R_CAPACITOR.2
unnamed: EPD_C1.1, J1.4
unnamed: J2.A5, R2-USB1.2
unnamed: EPD_C2.1, J1.5
unnamed: EPD_C6.1, J1.18
unnamed: EPD_C7.1, J1.19
unnamed: EPD_C8.1, J1.20
unnamed: C_DELAY.1, IC1.5 (CT)
unnamed: EPD_C10.1, J1.22
unnamed: C4.1, D3.2 (A), D4.1 (K)
unnamed: EPD_C12.1, J1.24
unnamed: R1_BAT.1, U5.1 (STAT)
unnamed: CHG_LED.C, R1_BAT.2
unnamed: R2_BAT.2, U5.5 (PROG)
PREVGH: D5.1 (K), EPD_C9.1, J1.21
PREVGL: D4.2 (A), EPD_C11.1, J1.23
RESE: J1.3, Q3.2 (S), R3.1
RESE': R2.2, R3.2, SJ1.2
RESET: C5.1, IC1.1 (VOUT), RESET_BUTTON.3, RESET_BUTTON.4, R_RESET.1, U2.3 (EN)
RTC_RST: U2.16 (IO18), U3.4 (!RST)
RX: TP_RX.TP, U2.24 (RXD0/GPIO17)
SCK: D10.2, J1.13, J4.P5 (CLK), R6.1, TP_SCK.TP, U1.6 (CLK), U2.6 (IO6)
SCL: J3.4, R2-PINH.1, SENSOR2.4 (SCK), U2.20 (IO22), U3.16 (SCL), U4.7 (SCL)
SDA: J3.3, R1-PINH.1, SENSOR2.3 (SDI), U2.19 (IO21), U3.15 (SDA), U4.8 (SDA)
SRC: C4.2, D5.2 (A), L1.1, Q3.3 (D)
SS_SD: D8.2, J4.P2 (CD/DAT3), R10.1, U2.4 (IO4)
TX: TP_TX.TP, U2.25 (TXD0/GPIO16)
USB_D+: D1.1 (I/O1_1), U2.14 (IO13)
USB_D-: D1.3 (I/O2_1), U2.13 (IO12)
VBAT: C2_BAT\.1, Q1.3 (D), TP_VBAT.TP, U4.2 (CELL), U4.3 (VDD), U5.3 (VBAT)
VBUS: C1_BAT.1, C4_USB.1, C5_USB.1, CHG_LED.A, D1.5 (VBUS), D2.2 (ANODE), PFMF.050.1.2, Q1.1 (G), R1_PWRUSB.2, TP_VBUS.TP, U5.4 (VIN)
VRTC: C8.1, C10_SUPERCAP.2, R_CAPACITOR.1, U3.14 (VBAT)
VUSB: J2.A4, J2.A9, J2.B4, J2.B9, PFMF.050.1.1

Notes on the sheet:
USB C connector & ESD protection
LDO Voltage Regulator
SD Card
ESP32 C6
Battery Charge Level
External NOR Flash 64MB
SPI ESD Protection Lines
Qwiic / Stemma QT
Test Pads
RTC Module DS3231SN
E-Paper Display Header
EPD Power
Environmental Sensor BME688
Voltage Supervisor + Reset & Boot / IO Button
Display Type Selector
E-Paper Drive Circuit
Li-Po Battery Charging Controller

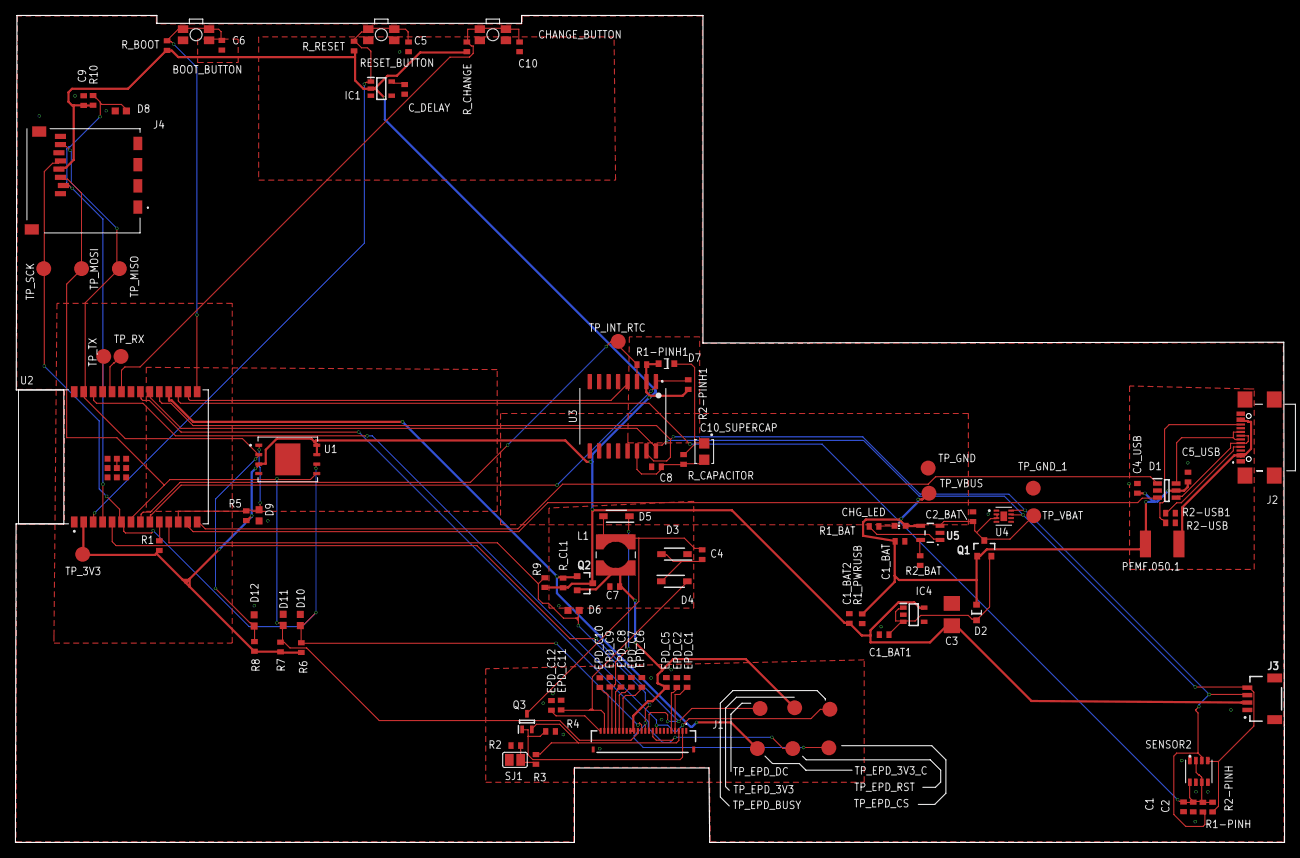
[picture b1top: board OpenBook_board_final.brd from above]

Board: 2 copper layers, 170.5 x 111.1 mm, 103 parts (0 on the bottom side), 55 nets.

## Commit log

2025-04-01 Create LICENSE
2025-04-04 Added most of the files - Mechanical was too big
    Had to make Mechanical a zip to fit it. README is left
2025-04-12 Update README.md with suggestions from issue
2025-04-14 Added updated board file
